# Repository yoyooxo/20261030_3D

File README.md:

# 20261030_3D — 讀卡機（單顆 nRF52840＋健保卡卡座）

只用一顆 nRF52840 SuperMini（nice!nano 相容）接 ISO 7816 卡座，焊在一塊 11 × 24 孔的洞洞板上。
卡座在板子背面、插卡口在上，模組的 USB-C 朝下，線全部在正面用 OK 線手焊，電池最後用雙面膠黏。

接線照老師的實物照片，不照 261103_nrf_card.pdf 的線路圖。

目前版本是 v9。

## 另一版：ICA-609 卡座麵包板轉接板 ＋ nRF52840

做一塊 T 字形單面 PCB，讓卡座直接插在麵包板上，再用杜邦線接 nRF52840。PCB 打樣檔、接線圖、3D 圖都在 [`card_reader_breadboard/`](card_reader_breadboard/README.md)。

**3D 整體（麵包板＋轉接板＋卡座＋nRF＋杜邦線＋電池）**

**PCB 正面／背面**

| 正面 | 背面 |
|---|---|
|  |  |

## 規格

| 項目 | 內容 |
|---|---|
| 洞洞板 | 27.9 × 61 mm，11 × 24 孔，2.54 mm 間距，直放 |
| 孔位標示 | (欄 c, 列 r)：c 為 1–11（左→右），r 為 1–24（下→上），正面俯視 |
| 卡座 J1 | 在板子背面，上緣是插卡口；8 支腳焊進 c8–c11 的第 24 列和第 8 列 |
| 模組 U1 | 轉 180°、USB-C 朝下；兩排 13 支腳全部插進 c1、c7 的第 1–13 列 |
| 電池 | LiPo 約 13 × 23 mm（照片估），在模組右邊，蓋在線上面 |

## 模組腳位（轉 180° 後）

| 列 | c1 | c7 |
|---|---|---|
| 1 | B+ | B- |
| 2 | RAW | P0.06 |
| 3 | GND | P0.08 |
| 4 | RST | GND |
| 5 | VCC | GND |
| 6 | P0.31 | P0.17 |
| 7 | P0.29 | P0.20 |
| 8 | P0.02 | P0.22 |
| 9 | P1.15 | P0.24 |
| 10 | P1.13 | P1.00 |
| 11 | P1.11 | P0.11 |
| 12 | P0.10 | P1.04 |
| 13 | P0.09 | P1.06 |

## 卡座腳位

| 位置 | c8 | c9 | c10 | c11 |
|---|---|---|---|---|
| 插卡口那排（第 24 列） | C5 GND | C6 | C7 I/O | C8 |
| 對面那排（第 8 列） | C1 VCC | C2 RST | C3 CLK | C4 |

C4、C6、C8 不接線，腳還是焊進洞，用來固定卡座。

## 接線（全部走正面，用 OK 線）

| 線號 | 起點 | 終點 | 用途 |
|---|---|---|---|
| K1 | VCC (c1,r5) | J1 C1 VCC (c8,r8) | +3V3_CARD，跨過模組 |
| K2 | B- (c7,r1) | J1 C5 GND (c8,r24) | 卡片 GND（照老師：接 B-） |
| K3 | P0.24 (c7,r9) | J1 C2 RST (c9,r8) | RST |
| K4 | P0.17 (c7,r6) | J1 C3 CLK (c10,r8) | CLK |
| K5 | P0.22 (c7,r8) | J1 C7 I/O (c10,r24) | I/O |
| K6 | P0.20 (c7,r7) | P0.22 (c7,r8) | I/O 兩腳併接（老師用短跳線） |
| K8 | P1.00 (c7,r10) | J1 SW1 DET | 插卡偵測 |
| K9 | J1 SW2 DET_G | GND (c7,r5) | 偵測開關接地 |
| K11 | 電池 ＋ | RAW (c1,r2) | VBAT（照老師：接 RAW，B+ 空著） |
| K12 | 電池 － | GND (c1,r3) | 電池負極 |

## 還沒確定的

| 項目 | 目前做法 | 怎麼確認 |
|---|---|---|
| C1–C8 的左右順序 | 照實物照片的接線判斷 | 焊之前用電表量 |
| 插卡口在哪一排 | 放上面 | 實際插卡看 |
| 偵測開關 SW1 / SW2 的腳位 | 畫在板子右緣外、第 8 列旁邊 | 看卡座實物 |
| 電池大小、厚度 | 約 13 × 23 × 4.5 mm | 量電池 |

## 檔案

| 檔案 | 用途 |
|---|---|
| [`讀卡機Layout_v9.png`](card_reader_nicenano/讀卡機Layout_v9.png) / [`.svg`](card_reader_nicenano/讀卡機Layout_v9.svg) | 目前的 Layout（含接線表） |
| [`讀卡機PCB_v9.kicad_pcb`](card_reader_nicenano/讀卡機PCB_v9.kicad_pcb) / [`.png`](card_reader_nicenano/讀卡機PCB_v9.png) | KiCad 洞洞板檔，OK 線畫在絲印層 |
| `讀卡機3D_v9_正面.png`、`_背面.png`、`_斜視.png` | KiCad 3D 圖（含模組、卡座、OK 線、電池） |
| `model_*.wrl` | 3D 模型（模組、卡座、OK 線、電池），PCB 用 `${KIPRJMOD}` 找，要跟 PCB 放同一個資料夾 |
| `gen_layout_card9.py`、`gen_pcb_card9.py` | 產生 v9 Layout 和 PCB／3D 模型的程式 |

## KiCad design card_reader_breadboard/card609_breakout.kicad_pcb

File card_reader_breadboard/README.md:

# ICA-609 卡座麵包板轉接板 ＋ nRF52840

把 Hamburg ICA-609 Type2 NO 卡座的 8 個觸點和偵測開關，轉接成兩排 1×5 排針，插在麵包板上，再用杜邦線接到 nRF52840 SuperMini（nice!nano 腳位）。接法照老師的板子。

**3D 整體（麵包板＋轉接板＋卡座＋nRF＋杜邦線＋電池）**

**PCB 正面／背面**

| 正面 | 背面 |
|---|---|
|  |  |

## PCB 規格

| 項目 | 內容 |
|---|---|
| 層數 | 單面板，銅箔只在正面（F.Cu） |
| 板材／板厚 | FR-4，1.6 mm |
| 外形 | T 字形，58.76 × 43.50 mm |
| 線寬／最小間距 | 0.40 mm／0.25 mm |
| 孔 | 20 個 Ø1.00 mm（卡座 10、排針 10），沒有過孔 |
| 打樣檔 | [`gerber/ICA609_breadboard_breakout_v1_gerber.zip`](gerber/ICA609_breadboard_breakout_v1_gerber.zip)，BOM 在 [`gerber/BOM.csv`](gerber/BOM.csv) |

卡座和排針的塑膠座都裝在背面（沒有銅的那面），腳穿到正面焊。DRC、ERC 沒有錯誤。

## 接線（麵包板 400 孔）

轉接板排針插 d1–d5（C1 C2 C3 C4 SW1）和 g1–g5（C5 C6 C7 C8 SW2）。模組插 d18–d30／h18–h30，USB-C 朝右。

| 線 | 從 | 到 | 用途 |
|---|---|---|---|
| W1 紅 | a1 | j26 | C1 VCC → VCC |
| W2 藍 | b2 | b22 | C2 RST → P0.24 |
| W3 綠 | a3 | a25 | C3 CLK → P0.17 |
| W4 紫 | b5 | b21 | SW1 → P1.00（插卡偵測） |
| W5 黑 | j1 | a30 | C5 GND → B- |
| W6 黃 | j3 | a23 | C7 I/O → P0.22 |
| W7 灰 | i5 | i28 | SW2 → GND |
| W8 黃 | b23 | b24 | P0.22 和 P0.20 併接 |
| W9 紅 | 電池＋ | j29 | RAW（B+ 空著） |
| W10 黑 | 電池－ | j28 | GND |

C4、C6、C8 不接。插模組前先對一下模組背面的印字。

## 圖

| 圖 | 內容 |
|---|---|
| [`接線圖_含nRF.png`](接線圖_含nRF.png) | 整體 Layout：轉接板＋卡座＋麵包板＋nRF＋接線表 |
| [`預覽_PCB.png`](預覽_PCB.png) | PCB Layout（銅箔＋絲印） |
| [`尺寸圖.png`](尺寸圖.png)、[`配置圖_麵包板.png`](配置圖_麵包板.png) | 尺寸、在麵包板上的位置與側視 |
| `立體_整體_斜視.png`、`立體_整體_正面.png` | 3D 整體（含 nRF、杜邦線、電池） |
| `立體_PCB_斜視.png`、`_正面.png`、`_背面.png` | 3D 空板 |
| `立體_PCB單板.png`、`立體_斜視.png` 等 | 3D：裝上卡座、排針；插在麵包板上（不含 nRF） |
| [`立體檢視.html`](立體檢視.html) | 下載後用瀏覽器打開，可以用滑鼠轉（需要網路） |

## 程式

KiCad 9 以上。腳本用環境變數 `KICAD_CLI` 找 kicad-cli，沒設就用 PATH 上的 `kicad-cli`。

| 檔案 | 用途 |
|---|---|
| `gen_breakout.py` | 產生 KiCad 專案（PCB、線路圖） |
| `gen_drawings.py` | 尺寸圖、麵包板配置圖 |
| `gen_wiring_nrf.py` | 接線圖（含 nRF） |
| `gen_scene.py`、`gen_scene_nrf.py` | 3D 圖 |
| `models3d.py` | 3D 方塊模型（卡座、排針、卡片、麵包板） |
| `check_dims.py` | 對照規格書檢查尺寸 |

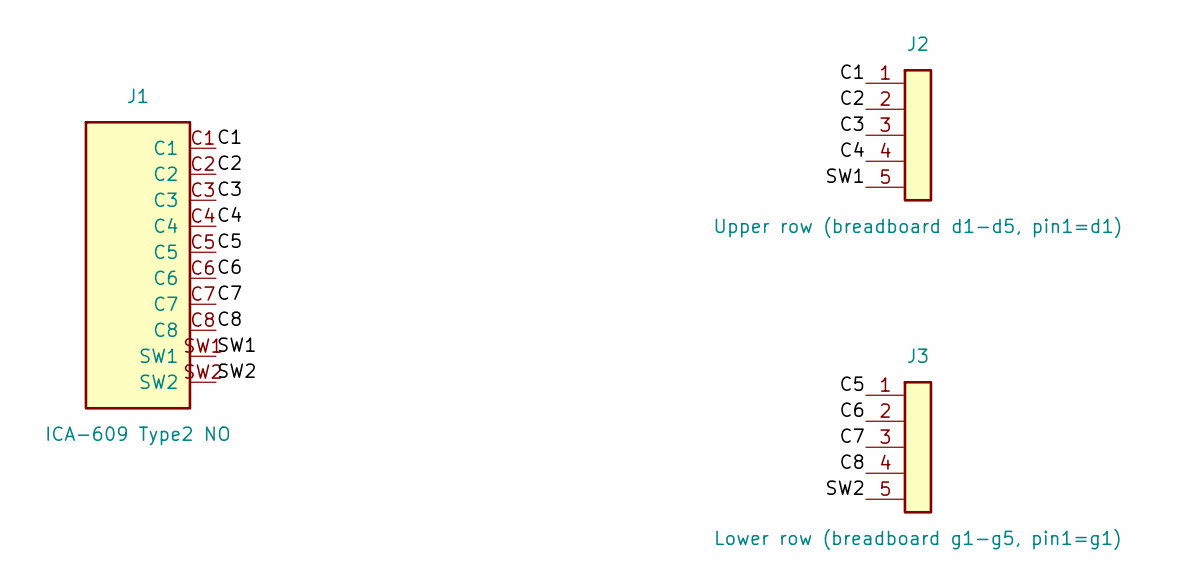
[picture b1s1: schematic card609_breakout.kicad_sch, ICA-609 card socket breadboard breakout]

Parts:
J1: ICA-609 Type2 NO; ICA-609_Type2
J2: Upper row (breadboard d1-d5, pin1=d1); PinHeader_1x05_P2.54
J3: Lower row (breadboard g1-g5, pin1=g1); PinHeader_1x05_P2.54

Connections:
/C1: J1.C1, J2.1 (C1)
/C2: J1.C2, J2.2 (C2)
/C3: J1.C3, J2.3 (C3)
/C4: J1.C4, J2.4 (C4)
/C5: J1.C5, J3.1 (C5)
/C6: J1.C6, J3.2 (C6)
/C7: J1.C7, J3.3 (C7)
/C8: J1.C8, J3.4 (C8)
/SW1: J1.SW1, J2.5 (SW1)
/SW2: J1.SW2, J3.5 (SW2)

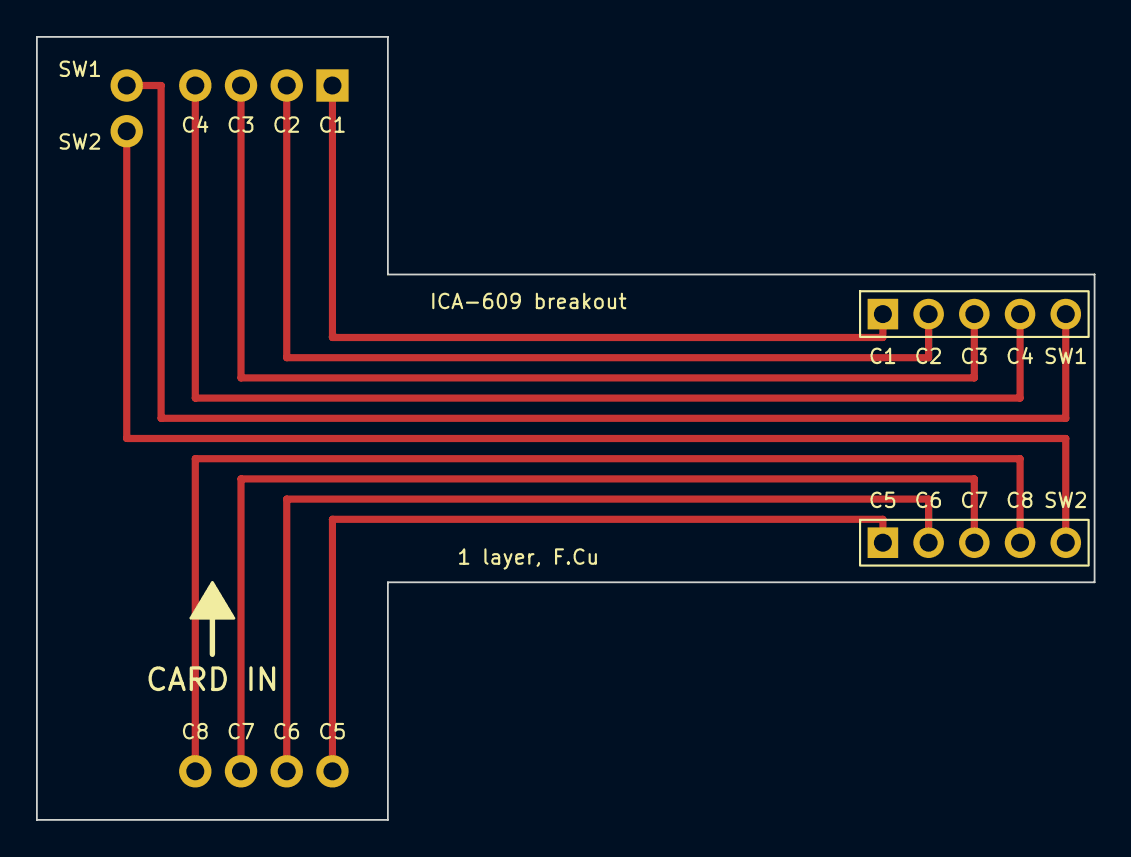
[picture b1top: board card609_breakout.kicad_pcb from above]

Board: 2 copper layers, 58.8 x 43.5 mm, 3 parts (1 on the bottom side), 10 nets.

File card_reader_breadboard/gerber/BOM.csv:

位號,數量,品名,規格,裝配面,備註
J1,1,IC 卡座,Hamburg ICA-609 Type2 NO（8 觸點 + 常開偵測開關，插件腳 Ø1.0）,背面（無銅面）,腳從背面穿上來、在正面（銅面）焊
J2,1,排針,1×5 直排公針 2.54 mm（標準 11.5 mm：下 6 / 塑膠 2.5 / 上 3）,塑膠座在背面,長腳朝下插麵包板 d1–d5，短腳在正面焊
J3,1,排針,1×5 直排公針 2.54 mm（同 J2）,塑膠座在背面,長腳朝下插麵包板 g1–g5，短腳在正面焊

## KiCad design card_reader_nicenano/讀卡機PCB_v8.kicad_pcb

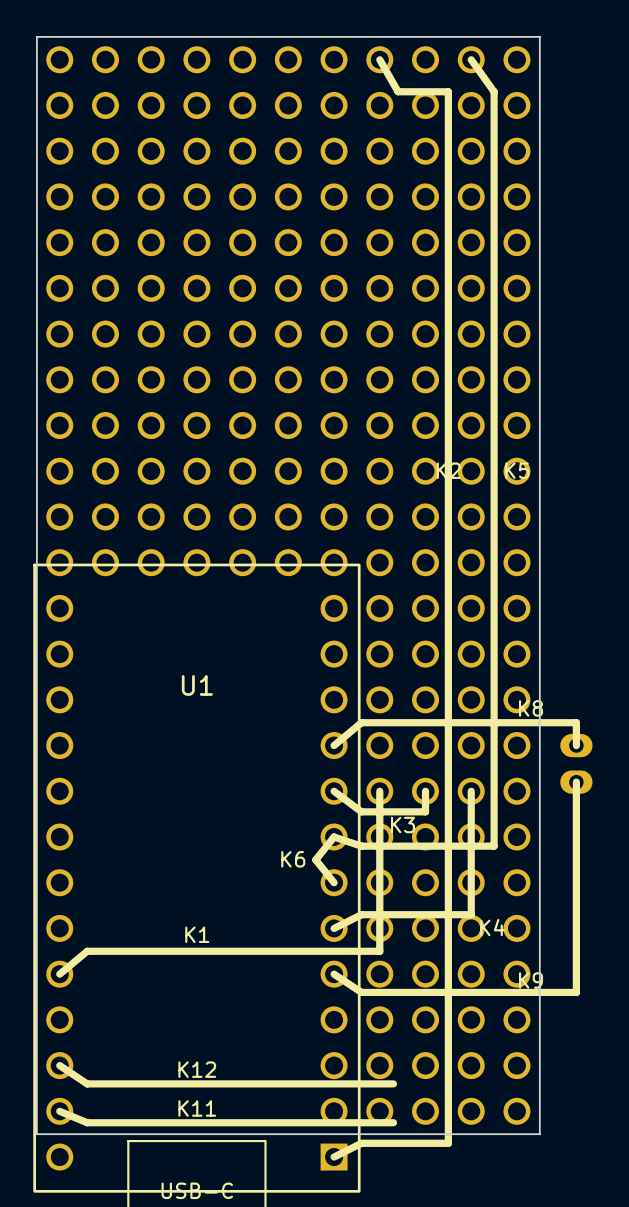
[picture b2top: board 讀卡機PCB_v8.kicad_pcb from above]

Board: 2 copper layers, 27.9 x 61.0 mm, 3 parts (1 on the bottom side), 6 nets, no tracks yet.

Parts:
J1: ISO7816 card socket (back side, slot at top); ISO7816_socket_62x42
PB1: perfboard 11x24; Perfboard_11x24
U1: nRF52840 SuperMini (nice!nano); SuperMini_nRF52840_13x2

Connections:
CLK: J1.C3, U1.6 (P0.17)
DET: J1.SW1, U1.10 (P1.00)
GND: J1.C5, J1.SW2, U1.1 (B-), U1.4 (GND), U1.5 (GND), U1.16 (GND)
IO: J1.C7, U1.7 (P0.20), U1.8 (P0.22)
RST: J1.C2, U1.9 (P0.24)
VCC_CARD: J1.C1, U1.18 (VCC)

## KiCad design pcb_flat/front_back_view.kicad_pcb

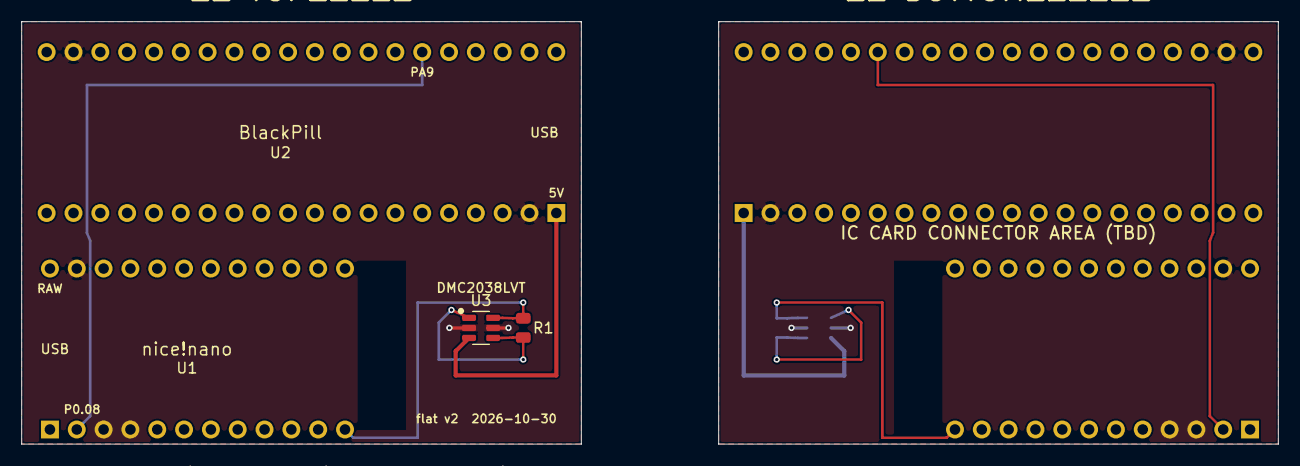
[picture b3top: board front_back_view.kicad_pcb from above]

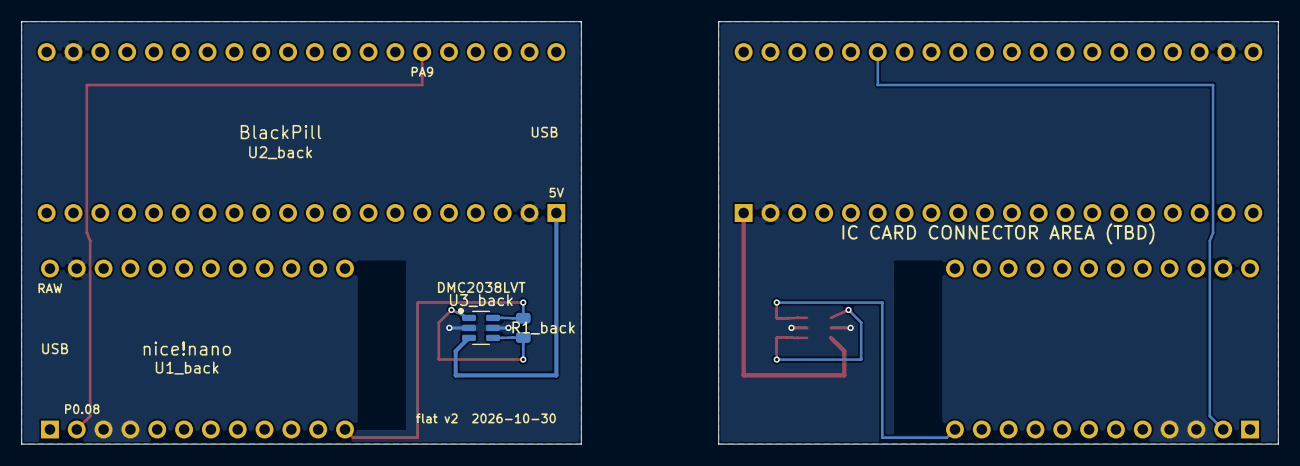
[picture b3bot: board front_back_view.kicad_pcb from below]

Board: 2 copper layers, 119.0 x 40.0 mm, 10 parts (5 on the bottom side), 5 nets.

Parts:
BT1, BT1_back: LiPo_30x25x5_on_BlackPill
R1, R1_back: R_0805
U1, U1_back: nice!nano_v2
U2, U2_back: WeAct_BlackPill
U3, U3_back: DMC2038LVT_SOT-23-6

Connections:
+5V: U2.L1, U2_back.L1, U3.3, U3_back.3
GND: U1.3, U1.4, U1.23, U1_back.3, U1_back.4, U1_back.23, U2.H19, U2.L2, U2_back.H19, U2_back.L2, U3.2, U3.5, U3_back.2, U3_back.5
N_D1: R1.2, R1_back.2, U1.12, U1_back.12, U3.6, U3_back.6
N_G1_D2: R1.1, R1_back.1, U3.1, U3.4, U3_back.1, U3_back.4
UART_PA9_P0.08: U1.2, U1_back.2, U2.H6, U2_back.H6

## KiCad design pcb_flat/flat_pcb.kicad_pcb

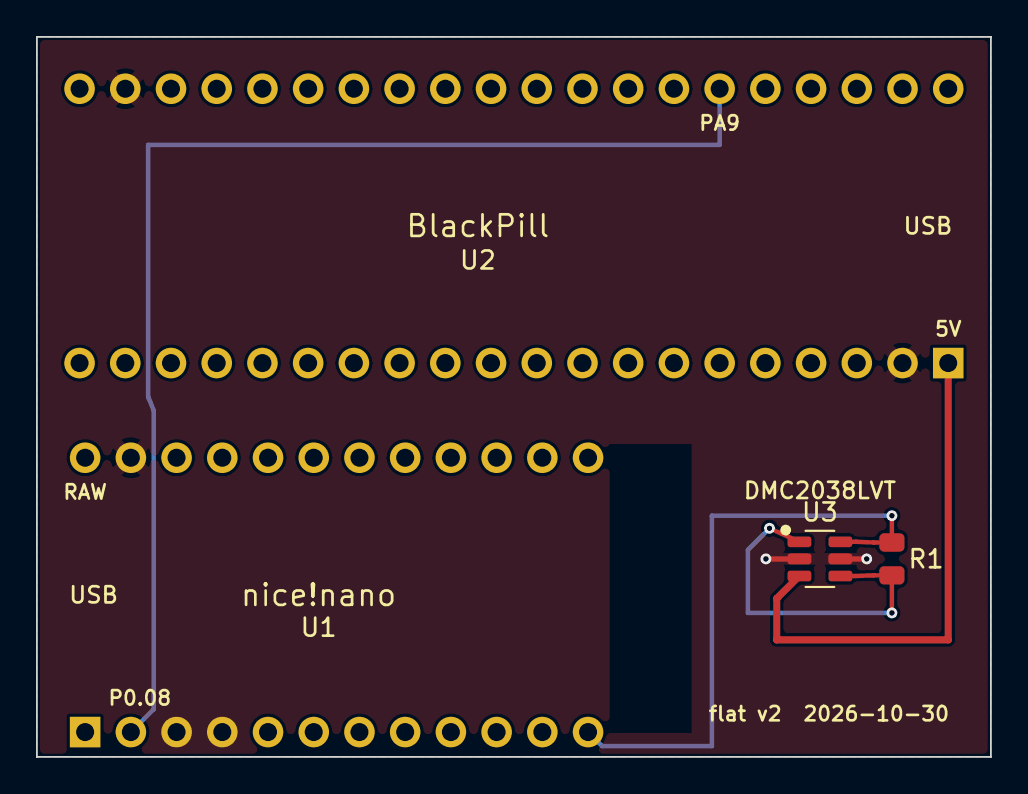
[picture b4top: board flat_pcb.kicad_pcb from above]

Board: 2 copper layers, 53.0 x 40.0 mm, 5 parts (0 on the bottom side), 5 nets.

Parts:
BT1: LiPo_30x25x5_on_BlackPill
R1: R_0805
U1: nice!nano_v2
U2: WeAct_BlackPill
U3: DMC2038LVT_SOT-23-6

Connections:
+5V: U2.L1, U3.3
GND: U1.3, U1.4, U1.23, U2.H19, U2.L2, U3.2, U3.5
N_D1: R1.2, U1.12, U3.6
N_G1_D2: R1.1, U3.1, U3.4
UART_PA9_P0.08: U1.2, U2.H6
